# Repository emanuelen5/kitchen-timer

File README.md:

# Kitchen timer

We're building a Kitchen timer!
The project is heavily inspired by [REST: Kitchen timer by mkdxdx [Hackaday.io]](https://hackaday.io/project/194386-rest-kitchen-timer).

## Features

* ⏱️ Allows several timers to run in parallel
* ⚡ Is battery powered and power efficient
* 🔌 Charged by USB-C
* 💻 Programmable through the same USB port
* 🐍 Easter eggs

## Hardware

* Atmega328P as microcontroller
* Rotary encoder for setting the time
* 16x16 LED matrix as display
* 32 kHz crystal for accurate timekeeping
* Passive buzzer for beeping

See the bill of material in the KiCAD project for the full details.

### Mechanical components

Additionally, you will need the following mechanical components for the assembly:

Description                                               | Qty
--------------------------------------------------------- |-----
Hexagon Socket Button Head Screw ISO 7380-1 - M3 x 16     | 4
Hexagon Socket Button Head Screw ISO 7380-1 - M2 x        | 3
Brass Threaded Insert M3                                  | 4
Brass Threaded Insert M2                                  | 3
Hexagon Socket Button Head Screw ISO 7380-1 - M2 x        | 3
3.7V Lipo battery 1000mAh, 10x20x50mm, JST XH2.54 2 pin   | 1

### Manufacturing / gerber files

If you want to build the PCB yourself, you can download the latest release of Gerber files from Github: <https://github.com/emanuelen5/kitchen-timer/releases/latest>

### Enclosure

The .stl files are available in [./enclosure](./enclosure/) so you can 3D-print the enclosure yourself.

## Software

You can flash the program directly using the ISP header on the board if you want (the same procedure as flashing the bootloader, below). But it's more convenient to add the bootloader so you don't have to open up the enclosure for each software update. Then you can instead program it over the USB-C connector.

For that, you need the bootloader firmware and programmer software which you can download from <https://github.com/emanuelen5/kitchen-timer/releases/tag/bootloader-v1.2.0>.

### Bootloader

To flash the microcontroller with the bootloader, you need `avrdude`.
Avrdude 7.3 can be downloaded from <https://github.com/avrdudes/avrdude/releases/tag/v7.3>. Make sure to add it to your `PATH`.

Connect your programmer of choice to the 6-pin in-system programmer (ISP) connector: \

<!--
Attribution:
["6- and 10-pin AVR ISP headers"](https://en.wikipedia.org/wiki/In-system_programming#/media/File:Isp_headers.svg)
by osiixy (2013-01-05), used under [CC BY 3.0](https://creativecommons.org/licenses/by/3.0/).
Adaptations: removed 10-pin header and some text; improved the contrast for dark
             mode.
-->

Then run the following command (replace `<programmer>` with your programmer of choice, like `usbtiny`):

```bash
# the bootloader.hex file needs to be in the current directory
avrdude -p atmega328p -c <programmer> -U flash:w:bootloader.hex:i \
  -U lfuse:w:0x62:m -U hfuse:w:0xD0:m -U efuse:w:0xFF:m
```

> [!TIP]
> Use `avrdude -c ?` to see which programmers are available

This flashes the bootloader and sets the required fuses for the bootloader.

After that you can disconnect the programmer and assemble the device.

### Programmer

Now that you have the bootloader on the device, you can use the USB-C cable for programming it by using the programmer application.

#### Dependencies

First you will need to install some packages that the programmer needs (files from <https://github.com/emanuelen5/kitchen-timer/releases/tag/bootloader-v1.2.0>).

```bash
pip install -r ./programmer/requirements.txt
```

You can now program the application onto the device through the bootloader!

### Upload firmware

Download the latest revision of the firmware (if you want to build it yourself, see [#Development](#development) below) from the releases <https://github.com/emanuelen5/kitchen-timer/releases>.

Connect the USB cable to the device, and then run

```bash
python3 ./programmer/programmer.py --hexfile firmware.hex
```

## Development

### Firmware

To build the firmware, you need `pio` which can be downloaded from <https://pypi.org/project/platformio/> or installed using `pip` (the official Package Installer for Python)

To build any of the environments, use the `pio` command, like

```bash
# builds the main application and puts it in .pio/builds/application/firmware.hex
pio run -e application
```

Then use the programmer to upload the firmware to the device.

## Background

Our kitchen timer is an iteration of [mkdxdx](https://hackaday.io/mkdxdx) project "REST: Kitchen timerREST: Kitchen timer". We wanted to keep the "dial" (rotate-to-set) concept and the 16x16 led matrix but do it with an ATmega328p and a custom PCB.
In the end we scrapped the dial since the design became too complicated, and settled on a simpler design.

### Motivation

Both [Erasmus Cedernaes](https://github.com/emanuelen5) and [Nicolas Perozzi](https://github.com/nperozzi) belong to [Stockholm Makerspace](https://www.makerspace.se/). On the same day, we messaged each other a link to mkdxdx​ project. We were very excited about building something that would be "practical" so we decided to team up and work on this together. Additionally, we share an interest in working with the AVR MCUs. This project is a nice blend of programming, electrical, mechanical, 3d printing, and design but, without feeling overwhelming.

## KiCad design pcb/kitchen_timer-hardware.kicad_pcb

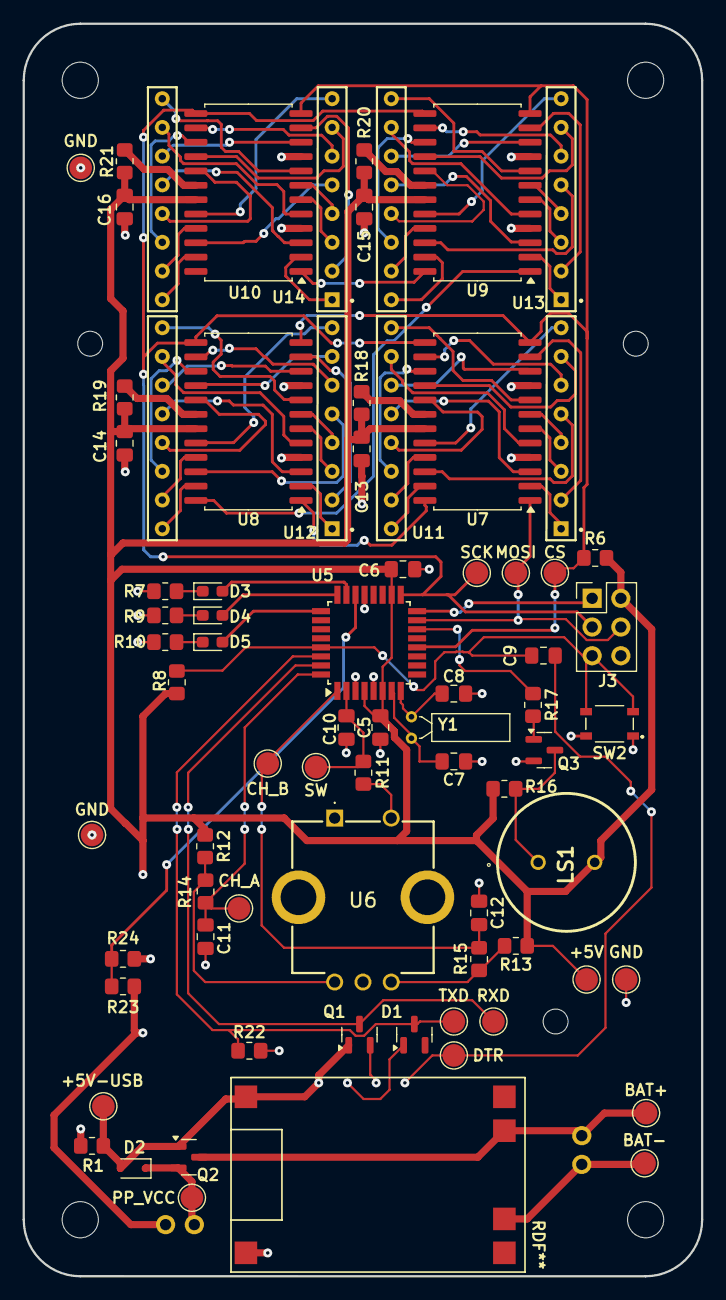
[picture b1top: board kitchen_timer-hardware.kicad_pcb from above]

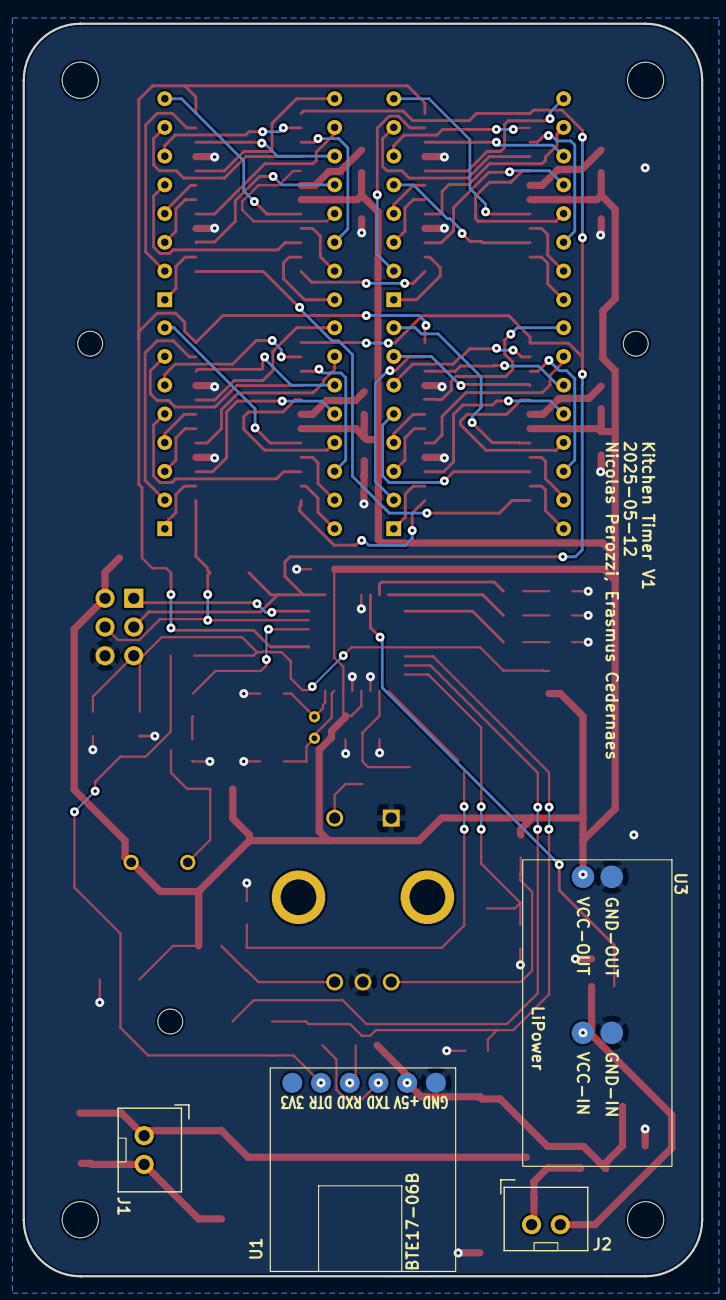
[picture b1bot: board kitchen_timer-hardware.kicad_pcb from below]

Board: 2 copper layers, 60.0 x 110.8 mm, 83 parts (4 on the bottom side), 106 nets.

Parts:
C5, C6, C9, C13, C14, C15, C16: 100nF; C_0805_2012Metric_Pad1.18x1.45mm_HandSolder
C7, C8: 22pF; C_0805_2012Metric_Pad1.18x1.45mm_HandSolder
C10, C11, C12: 10nF; C_0805_2012Metric_Pad1.18x1.45mm_HandSolder
D1: BAS40; SOT-23
D2: PMEG4010CEJ; D_SOD-323F
D3, D4, D5: Red test LED; LED_0603_1608Metric_Pad1.05x0.95mm_HandSolder
H1, H2, H7: MountingHole; MountingHole_2.2mm_M2
H3, H4, H5, H6: MountingHole; MountingHole_3.2mm_M3
J1: Conn_01x02; JST_XH_1x02_P2.54mm_Vertical
J2: Conn_01x02_Pin; JST_XH_1x02_P2.54mm_Vertical
J3: AVR-ISP-6; PinHeader_2x03_P2.54mm_Vertical
LS1: PS1240P02CT3; PS1240P02BT
Q1: JSM2302; SOT-23
Q2: IRLML6402; SOT-23
Q3: MMBT3904; MMBT3904 (SOT-23)
R1, R6, R8, R11, R12, R13, R14, R15, R22: 10k; R_0805_2012Metric_Pad1.20x1.40mm_HandSolder
R7, R9, R10, R16, R17: 1k; R_0805_2012Metric_Pad1.20x1.40mm_HandSolder
R18, R19, R20, R21: 62K; R_0805_2012Metric_Pad1.20x1.40mm_HandSolder
R23: 3.3M; R_0805_2012Metric_Pad1.20x1.40mm_HandSolder
R24: 1M; R_0805_2012Metric_Pad1.20x1.40mm_HandSolder
SW2: SKRPACE010; SW_SKRPACE010
TP1: MOSI; TestPoint_Pad_D2.0mm
TP2: TXD; TestPoint_Pad_D2.0mm
TP3: SCK; TestPoint_Pad_D2.0mm
TP4: RXD; TestPoint_Pad_D2.0mm
TP5: CS; TestPoint_Pad_D2.0mm
TP6: DTR; TestPoint_Pad_D2.0mm
TP7: +5V-USB; TestPoint_Pad_D2.0mm
TP8, TP14, TP15: GND; TestPoint_Pad_D2.0mm
TP9: CH_A; TestPoint_Pad_D2.0mm
TP10: CH_B; TestPoint_Pad_D2.0mm
TP11: SW; TestPoint_Pad_D2.0mm
TP12: +5V; TestPoint_Pad_D2.0mm
TP13: PP_VCC; TestPoint_Pad_D2.0mm
TP16: BAT+; TestPoint_Pad_D2.0mm
TP17: BAT-; TestPoint_Pad_D2.0mm
U1: CH340E UART Module; CH340E_UART_BREAKOUT
U2: TP4056 breakout; TP4056_BREAKOUT
U3: SparkFun_LiPower
U5: ATMEGA328P-AU; TQFP-32_7x7mm_P0.8mm
U6: PEC11R-4215F-S0024; PEC11R4215FS0024
U7, U8, U9, U10: MAX7219; SOIC-24W_7.5x15.4mm_P1.27mm
U11, U12, U13, U14: KWM-20882CUYB
Y1: Crystal-32kHz; Crystal_C26-LF_D2.1mm_L6.5mm_Horizontal

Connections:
+5V: C5.1, C6.1, C13.1, C14.1, C15.1, C16.1, J3.2 (VCC), LS1.2, R6.1, R8.1, R12.1, R13.1, R16.2, R18.1, R19.1, R20.1, R21.1, TP12.1, U3.3 (VCC_OUT), U5.4 (VCC), U5.6 (VCC), U5.18 (AVCC), U7.19 (V+), U8.19 (V+), U9.19 (V+), U10.19 (V+)
/+5V Boost Converter/BAT_VOLT: R23.2, R24.1, U5.22 (ADC7)
/+5V Boost Converter/PP_VCC: D2.1 (K), J2.1, Q2.2 (S), TP13.1
/BMS & Power Path/+5V-USB: D2.2 (A), Q1.1 (G), Q2.1 (G), R1.2, TP7.1, U1.5 (+5V), U2.1 (IN+)
/BMS & Power Path/BAT+: J1.1, Q2.3 (D), TP16.1, U2.4 (B+)
/BMS & Power Path/BAT-: J1.2, TP17.1, U2.5 (B-)
/LED Matrices Drivers/CS: R6.2, TP5.1, U5.12 (PB0), U7.12 (LOAD), U8.12 (LOAD), U9.12 (LOAD), U10.12 (LOAD)
/LED Matrices Drivers/MOSI: J3.4 (MOSI), TP1.1, U5.15 (PB3), U7.1 (DIN)
/LED Matrices Drivers/Mat1A.DIG_0: U7.2 (DIG_0), U11.01 (R1)
/LED Matrices Drivers/Mat1A.DIG_1: U7.11 (DIG_1), U11.02 (R2)
/LED Matrices Drivers/Mat1A.DIG_2: U7.6 (DIG_2), U11.03 (R3)
/LED Matrices Drivers/Mat1A.DIG_3: U7.7 (DIG_3), U11.04 (R4)
/LED Matrices Drivers/Mat1A.DIG_4: U7.3 (DIG_4), U11.12 (R5)
/LED Matrices Drivers/Mat1A.DIG_5: U7.10 (DIG_5), U11.11 (R6)
/LED Matrices Drivers/Mat1A.DIG_6: U7.5 (DIG_6), U11.10 (R7)
/LED Matrices Drivers/Mat1A.DIG_7: U7.8 (DIG_7), U11.09 (R8)
/LED Matrices Drivers/Mat1A.SEG_A: U7.14 (SEG_A), U11.06 (C2)
/LED Matrices Drivers/Mat1A.SEG_B: U7.16 (SEG_B), U11.07 (C3)
/LED Matrices Drivers/Mat1A.SEG_C: U7.20 (SEG_C), U11.08 (C4)
/LED Matrices Drivers/Mat1A.SEG_D: U7.23 (SEG_D), U11.16 (C5)
/LED Matrices Drivers/Mat1A.SEG_DP: U7.22 (SEG_DP), U11.05 (C1)
/LED Matrices Drivers/Mat1A.SEG_E: U7.21 (SEG_E), U11.15 (C6)
/LED Matrices Drivers/Mat1A.SEG_F: U7.15 (SEG_F), U11.14 (C7)
/LED Matrices Drivers/Mat1A.SEG_G: U7.17 (SEG_G), U11.13 (C8)
/LED Matrices Drivers/Mat1B.DIG_0: U8.2 (DIG_0), U12.01 (R1)
/LED Matrices Drivers/Mat1B.DIG_1: U8.11 (DIG_1), U12.02 (R2)
/LED Matrices Drivers/Mat1B.DIG_2: U8.6 (DIG_2), U12.03 (R3)
/LED Matrices Drivers/Mat1B.DIG_3: U8.7 (DIG_3), U12.04 (R4)
/LED Matrices Drivers/Mat1B.DIG_4: U8.3 (DIG_4), U12.12 (R5)
/LED Matrices Drivers/Mat1B.DIG_5: U8.10 (DIG_5), U12.11 (R6)
/LED Matrices Drivers/Mat1B.DIG_6: U8.5 (DIG_6), U12.10 (R7)
/LED Matrices Drivers/Mat1B.DIG_7: U8.8 (DIG_7), U12.09 (R8)
/LED Matrices Drivers/Mat1B.SEG_A: U8.14 (SEG_A), U12.06 (C2)
/LED Matrices Drivers/Mat1B.SEG_B: U8.16 (SEG_B), U12.07 (C3)
/LED Matrices Drivers/Mat1B.SEG_C: U8.20 (SEG_C), U12.08 (C4)
/LED Matrices Drivers/Mat1B.SEG_D: U8.23 (SEG_D), U12.16 (C5)
/LED Matrices Drivers/Mat1B.SEG_DP: U8.22 (SEG_DP), U12.05 (C1)
/LED Matrices Drivers/Mat1B.SEG_E: U8.21 (SEG_E), U12.15 (C6)
/LED Matrices Drivers/Mat1B.SEG_F: U8.15 (SEG_F), U12.14 (C7)
/LED Matrices Drivers/Mat1B.SEG_G: U8.17 (SEG_G), U12.13 (C8)
/LED Matrices Drivers/Mat2A.DIG_0: U9.2 (DIG_0), U13.01 (R1)
/LED Matrices Drivers/Mat2A.DIG_1: U9.11 (DIG_1), U13.02 (R2)
/LED Matrices Drivers/Mat2A.DIG_2: U9.6 (DIG_2), U13.03 (R3)
/LED Matrices Drivers/Mat2A.DIG_3: U9.7 (DIG_3), U13.04 (R4)
/LED Matrices Drivers/Mat2A.DIG_4: U9.3 (DIG_4), U13.12 (R5)
/LED Matrices Drivers/Mat2A.DIG_5: U9.10 (DIG_5), U13.11 (R6)
/LED Matrices Drivers/Mat2A.DIG_6: U9.5 (DIG_6), U13.10 (R7)
/LED Matrices Drivers/Mat2A.DIG_7: U9.8 (DIG_7), U13.09 (R8)
/LED Matrices Drivers/Mat2A.SEG_A: U9.14 (SEG_A), U13.06 (C2)
/LED Matrices Drivers/Mat2A.SEG_B: U9.16 (SEG_B), U13.07 (C3)
/LED Matrices Drivers/Mat2A.SEG_C: U9.20 (SEG_C), U13.08 (C4)
/LED Matrices Drivers/Mat2A.SEG_D: U9.23 (SEG_D), U13.16 (C5)
/LED Matrices Drivers/Mat2A.SEG_DP: U9.22 (SEG_DP), U13.05 (C1)
/LED Matrices Drivers/Mat2A.SEG_E: U9.21 (SEG_E), U13.15 (C6)
/LED Matrices Drivers/Mat2A.SEG_F: U9.15 (SEG_F), U13.14 (C7)
/LED Matrices Drivers/Mat2A.SEG_G: U9.17 (SEG_G), U13.13 (C8)
/LED Matrices Drivers/Mat2B.DIG_0: U10.2 (DIG_0), U14.01 (R1)
/LED Matrices Drivers/Mat2B.DIG_1: U10.11 (DIG_1), U14.02 (R2)
/LED Matrices Drivers/Mat2B.DIG_2: U10.6 (DIG_2), U14.03 (R3)
/LED Matrices Drivers/Mat2B.DIG_3: U10.7 (DIG_3), U14.04 (R4)
/LED Matrices Drivers/Mat2B.DIG_4: U10.3 (DIG_4), U14.12 (R5)
/LED Matrices Drivers/Mat2B.DIG_5: U10.10 (DIG_5), U14.11 (R6)
/LED Matrices Drivers/Mat2B.DIG_6: U10.5 (DIG_6), U14.10 (R7)
/LED Matrices Drivers/Mat2B.DIG_7: U10.8 (DIG_7), U14.09 (R8)
/LED Matrices Drivers/Mat2B.SEG_A: U10.14 (SEG_A), U14.06 (C2)
/LED Matrices Drivers/Mat2B.SEG_B: U10.16 (SEG_B), U14.07 (C3)
/LED Matrices Drivers/Mat2B.SEG_C: U10.20 (SEG_C), U14.08 (C4)
/LED Matrices Drivers/Mat2B.SEG_D: U10.23 (SEG_D), U14.16 (C5)
/LED Matrices Drivers/Mat2B.SEG_DP: U10.22 (SEG_DP), U14.05 (C1)
/LED Matrices Drivers/Mat2B.SEG_E: U10.21 (SEG_E), U14.15 (C6)
/LED Matrices Drivers/Mat2B.SEG_F: U10.15 (SEG_F), U14.14 (C7)
/LED Matrices Drivers/Mat2B.SEG_G: U10.17 (SEG_G), U14.13 (C8)
/LED Matrices Drivers/SCK: J3.3 (SCK), TP3.1, U5.17 (PB5), U7.13 (CLK), U8.13 (CLK), U9.13 (CLK), U10.13 (CLK)
/Microcontroller/DTR: C9.1, TP6.1, U1.2 (DTR)
/Microcontroller/ENCODER_CH_A: C11.1, R14.2, TP9.1, U5.32 (PD2)
/Microcontroller/ENCODER_CH_B: C12.1, R15.2, TP10.1, U5.1 (PD3)
/Microcontroller/MCU_RXD: D1.3 (K), R22.1, TP2.1, U5.30 (PD0)
/Microcontroller/MCU_TXD: Q1.3 (D), TP4.1, U5.31 (PD1)
/Microcontroller/MISO: J3.1 (MISO), U5.16 (PB4)
/Microcontroller/RESET: C9.2, J3.5 (~RST), R8.2, SW2.3, SW2.4, U5.29 (~RESET/PC6)
/Microcontroller/SPEAKER: R17.1, U5.14 (PB2)
/Microcontroller/SW: C10.1, R11.2, TP11.1, U5.2 (PD4)
/Microcontroller/TEST_LED1: D3.2 (A), U5.23 (PC0)
/Microcontroller/TEST_LED2: D4.2 (A), U5.24 (PC1)
/Microcontroller/TEST_LED3: D5.2 (A), U5.25 (PC2)
/Microcontroller/XTAL1: C7.1, U5.7 (XTAL1/PB6), Y1.1
/Microcontroller/XTAL2: C8.1, U5.8 (XTAL2/PB7), Y1.2 (CRYSTAL_2)
GND: C5.2, C6.2, C7.2, C8.2, C10.2, C11.2, C12.2, C13.2, C14.2, C15.2, C16.2, J3.6 (GND), Q3.2 (E), R1.1, R7.2, R9.2, R10.2, R22.2, R24.2, SW2.1, SW2.2, TP8.1, TP14.1, TP15.1, U1.6 (GND), U2.2 (IN-), U3.2 (GND-IN), U3.4 (GND_OUT), U5.3 (GND), U5.5 (GND), U5.21 (GND), U6.1 (COM), U6.C1 (COMMON), U7.4 (GND), U7.9 (GND), U8.4 (GND), U8.9 (GND), U9.4 (GND), U9.9 (GND), U10.4 (GND), U10.9 (GND)
unnamed: D1.1 (A), U1.4 (TXD)
unnamed: D3.1 (K), R7.1
unnamed: D4.1 (K), R9.1
unnamed: D5.1 (K), R10.1
unnamed: Q1.2 (S), U1.3 (RXD)
unnamed: Q3.1 (B), R17.2
unnamed: LS1.1, Q3.3 (C), R16.1
unnamed: R12.2, R14.1, U6.A1 (CHANNEL_A)
unnamed: R13.2, R15.1, U6.B1 (CHANNEL_B)
unnamed: R11.1, U6.2 (NO)
unnamed: U7.24 (DOUT), U8.1 (DIN)
unnamed: R18.2, U7.18 (ISET)
unnamed: U8.24 (DOUT), U9.1 (DIN)
unnamed: R19.2, U8.18 (ISET)
unnamed: R20.2, U9.18 (ISET)
unnamed: U9.24 (DOUT), U10.1 (DIN)
unnamed: R21.2, U10.18 (ISET)
PP_VCC_after_switch: J2.2, R23.1, U3.1 (VCC_IN)

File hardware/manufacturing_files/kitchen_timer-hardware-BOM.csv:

"Reference","Value","Footprint","Qty","Supplier Part #"
"C5,C6,C9,C13,C14,C15,C16","100nF","Capacitor_SMD:C_0805_2012Metric_Pad1.18x1.45mm_HandSolder","7","C77082"
"C7,C8","22pF","Capacitor_SMD:C_0805_2012Metric_Pad1.18x1.45mm_HandSolder","2","C1804"
"C10,C11,C12","10nF","Capacitor_SMD:C_0805_2012Metric_Pad1.18x1.45mm_HandSolder","3","C1710"
"D1","BAS40","Package_TO_SOT_SMD:SOT-23","1"," C77289"
"D2","PMEG4010CEJ","Diode_SMD:D_SOD-323F","1","C50704"
"D3,D4,D5","Red test LED","LED_SMD:LED_0603_1608Metric_Pad1.05x0.95mm_HandSolder","3","C965799"
"Q1","JSM2302","Package_TO_SOT_SMD:SOT-23","1"," C916403"
"Q2","IRLML6402","Package_TO_SOT_SMD:SOT-23","1","C2593"
"Q3","MMBT3904","kitchen_timer:MMBT3904 (SOT-23)","1"," C7420353"
"R1,R6,R8,R11,R12,R13,R14,R15","10k","Resistor_SMD:R_0805_2012Metric_Pad1.20x1.40mm_HandSolder","8","C17414"
"R7,R9,R10,R16,R17","1k","Resistor_SMD:R_0805_2012Metric_Pad1.20x1.40mm_HandSolder","5","C17513"
"R18,R19,R20,R21","62K","Resistor_SMD:R_0805_2012Metric_Pad1.20x1.40mm_HandSolder","4","C17783"
"SW2","SKRPACE010","kitchen_timer:SW_SKRPACE010","1","C139797"
"U5","ATMEGA328P-AU","Package_QFP:TQFP-32_7x7mm_P0.8mm","1","C14877"
"U7,U8,U9,U10","MAX7219","Package_SO:SOIC-24W_7.5x15.4mm_P1.27mm","4","C9964"
"LS1","PS1240P02CT3","kitchen_timer:PS1240P02BT","1"," C76873"
"U6","PEC11R-4215F-S0024","kitchen_timer:PEC11R4215FS0024","1","C143790"

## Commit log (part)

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2025-07-09 just added a TODO comment
2025-07-09 Made should_toggle... variables for clarity
2025-07-09 moved #include to the cpp file
2025-07-10 Completed the definition of the Hour Indicator
2025-07-10 changed the function name to draw_active_timer_indicator()
2025-07-10 added init_led_counter() to main
2025-07-15 added application_view enum and new variables into application_t
2025-07-16 Only call render once
2025-07-17 Created the fucntion change_view()
2025-07-17 Made const a couple of variables
2025-07-17 moved some #define to the confi.h file
2025-07-17 Create an Application Environment
2025-07-17 Added the open_new_timer()
2025-07-18 Simplified the render_active_timer_view() a little.
2025-07-20 Fixed a bug with allocating memory for the state machines
2025-07-20 changed the increment_current_time() for decrement_current_time
2025-07-21 I am getting rid of a redundant variable in the application_t struct
2025-07-23 Removed a variable that was not doing anything
2025-07-23 Made the press rotation skip timers that are in IDLE state.
2025-07-24 Modified service_application() so the active timer moves to the ringing timer.
2025-07-25 I made the RINGING state also blink the timer numbers also I restructured that blinking part of the code.
2025-07-25 bug: I added the set_state() function to pass from RINGING to IDLE
2025-07-25 I moved the digits offset one more column to the left to use the space better.
2025-07-26 Simplified the blinking of the Timer Indicator and Timer Digits by defining a struct for blink_state.
2025-07-26 Simplified a variable in draw_timers_indicator()
2025-07-27 Removed target_time from timer lib. It was unnecessary.
2025-07-27 Changes on the Unit test to include the SET_TIME state.
2025-07-27 changes to Unit test.
2025-07-27 Added sentinel value to application_view_t enum.
2025-07-27 Changed name of open_new_timer() to try_to_open_new_timer().
2025-07-27 Fixed a mistake in the name of try_to_open_new_timer() function
2025-07-28 Made the application_handle_event() into a set of special cases else, pass to the active state machine.
2025-07-28 created reset_state_machine()
2025-09-08 Added handle_encoder_rotation(), removed .pyc files and added that extension to .gitignore.
2025-09-08 changed from calculating interval to recording timestamps and bitshifting instead of division
2025-09-09 Created is_fast_step() in rotary-encoder.cpp
2025-09-09 Added the handling of the new events to the state machine
2025-09-10 Modified main.cpp in rotary-encoder environment
2025-09-10 Created the serial_commands library files
2025-09-10 Added str_equals() function in str-helper lib
2025-09-10 drafted the command_callbacks struct
2025-09-10 Added trim_string() to str-helper lib
2025-09-10 Break up into several functions
2025-09-10 Create type for speed of rotation
2025-09-10 Remove dead code
2025-09-10 Use event speed type
2025-09-10 Make fast rotations increment time faster than slow (#107)
    * Added handle_encoder_rotation(), removed .pyc files and added that
    extension to .gitignore.
    * Used a const instead of a preprocessor define
    * changed from calculating interval to recording timestamps and bitshifting instead of division
    * Added functionality: When it is over 1hr, the steps are 1min and if it is fast_steps, it is 5 mins steps
    * Created is_fast_step() in rotary-encoder.cpp
2025-09-12 Read pins earlier after interrupt
2025-09-12 Fix 'press, then rotate' bug
    When pressing and then rotating in short sequence, it would sometimes
    not register the first press, unless you waited for a long time between
    them.
    Fixes #96
2025-09-13 Shorten time before starting main application to ~0.6 secondds
2025-09-13 Make the timer beep when it finishes
2025-09-13 Fix linker issue for native tests
2025-09-14 Remove dead code in toneAC
    Fixes #97
2025-09-14 fixup! Repeat the beeps for an amount of times
2025-09-14 Fix: don't skip first note in melody
2025-09-14 fixup! Make the beat slightly shorter
2025-09-14 Clean up toneAC and make less generalized
    We have no use of those things, and they just take up storage space
    (plus an unused interrupt). It's more generalized than needed for our
    purpose.
    Fixes #97
2025-09-14 Rename functions
2025-09-14 Distinguish between time of hours and minutes
2025-09-20 Rename program->flash
2025-09-20 Remove TODOs
    It's better to track them as an issue. It only confuses the reader.
2025-09-20 Move files to Github
2025-09-23 Added the on_line_received() function (Dependency inversion) to separate UART logic form business logic.
2025-09-23 Added command + argument functionality
2025-09-24 In change_original_time() from timer lib, I changed the step argument from int16_t to int32_t to allow for a larger number of steps. This was needed for the parse_time_string(char* arg, uint32_t *ste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
2025-09-24 Added parse_time_string()
2025-09-24 Added commands for 'timer play', 'timer pause', 'timer reset'
2025-09-26 Modified UART_printf() to accept %d format with leading zeros
2025-09-30 Fixed a build problem on state_machine env.
2025-09-30 Created file for testing the serial_commands lib.
2025-10-01 Added setup brightness command
2025-10-01 Added setup volumne command.
2025-10-01 Fixed a bug in setup volume command.
2025-10-02 Added test buzzer command.
2025-10-03 moved led on/off into test commnad
2025-10-06 Use higher frequencies since the buzzer is tuned for 4kHz
2025-10-10 Make UART RX snappier
    Service the UART RX until it's empty.
2025-10-10 Remove unused declarations
2025-10-10 Autoformat files
2025-10-10 Remove redundant sketch
    The test cases already cover the counter, so the sketch itself doesn't
    serve a purpose anymore. There are several other sketches that offer
    similar and more complete examples.
2025-10-11 Implement simple power saving
    - Dim the display after 30 seconds of inactivity
    - Turn off the display after being dim for a minute without any timer
    running
    - Deep sleep not yet implemented
2025-10-11 Fixing a function that I deleted by mistake in during the merge
2025-10-14 added *.code-workspace to .gitignore
2025-10-15 Fix crash when interacting with rotary knob during power-on
    Interrupts got fired before all callbacks were initialized, leading to
    undefined behavior - and crashes.
    A crash could occur with the following conditions:
    1. Power on the device
    2. Rotate the knob (this would mark the INT1 interrupt as pending),
    before `init_hw_rotary_encoder()` is executed.
2025-10-17 Moved all remaining cbs and the command_callback_t struct definition.
2025-10-19 Break out function
2025-10-19 Remove unreachable statement
2025-10-24 Use compact conditional style
2025-10-24 Start writing tests for the main application
2025-10-29 Used bool in pad_zero variable
2025-10-29 Implemented unrecoginized_command() callback.
2025-10-31 Made pad_zero a bool
2025-10-31 Removed forgotten comments on wdt_bootloader_disable()
2025-10-31 Changed eeprom_write_byte() to eeprom_update_byte().
    The update function only writes if the new value is differen than the one stored. Better for saving writes in EEPROM.
2025-10-31 Changes the help_cmd cb to just help.
2025-10-31 Modified unrecoginized_command() to have a custom error message for brightness and volume setting.
2025-11-02 Fixed some problems with the merge.
2025-11-09 Go back to sleep if woken by an interrupt without user activity
    Turns out this is actually a completely valid case!
    The rotary encoder takes 4 substeps for each rotation, which thus makes
    up a very small angle of rotation. And that makes it likely to happen
    when just picking up the device, or shaking it lightly.
    If this happens, we'll quite quickly go to sleep again when the
    interrupts stop happening. That way we make sure to go down to low power
2025-11-09 Set int width to atmega328p size
    This way we can test natively using the same sized int.
2025-11-10 Changes to test_serial_commands unit test.
2025-11-12 Changes on the unit test
    Simplified the tests and put all the testing variables into a struct to make it easier to reset between tests.
2025-11-28 Changed activer_timer_view() in render module
2025-11-30 Added default state to render_active_timer_view()
2025-11-30 Added the change of target time during RUNNING and PAUSE mode.
2025-11-30 Created settings_menu module files
2025-11-30 Moved event_t to its own module.
2025-12-01 Started the settings_menu logic
2025-12-01 Added draw bitmap
2026-01-10 Reorganized the bytes in icon_brightness
2026-01-10 Removed a blank option after the back option
2026-01-10 Created the change_settings_views_callbacks_t struct to handle all settings_menu callbacks to change views.
2026-01-10 Added all settings views to application_view_t
2026-01-11 Removed an unnecessary function
2026-01-11 Changed change_to_a_setting_view_cb
2026-01-11 Created volume_setting_event_handling
2026-03-02 Make a separate function for getting icons
2026-03-04 Simplified current_menu_position and selected_setting for clarity
2026-03-04 Applied autoformat to render.cpp
2026-03-04 Fixed brightness over and underflow. Co-authored-by: Erasmus Cedernaes <github@emaus.dev>
2026-03-04 Moved down the icons
2026-03-04 Removed the MAX_BRIGHTNESS config
2026-03-04 We changed the test_buzzer melody on serial commands
2026-03-04 Fix mistake in 23736b24c2f617866299bd969b5b6892af003ecd
2026-03-06 Created the ten_beeps melody to avoid loading a repeated sequence at startup.
2026-03-06 Implemented the render function for the melody setting menu.
2026-03-06 Added comment to eeprom address enum
2026-03-06 Implemented the M1, M2,... render for melody settings
2026-03-11 Set CS to correct value before enabling its output
2026-03-11 Fixed saving volume
2026-03-11 Changed to reset_active_state_machine() when timer goes from RINGING to SET_TIME
2026-03-11 Fixed state machine test
2026-03-11 Break out function to describe intent and give single responsibility
2026-03-11 Go back to the settings from battery view
2026-03-14 Added Tx resistor, voltage devider for battery voltage mesurement.
2026-03-16 Cap the brightness if memory is uninitialized/corrupt
2026-03-22 Print debug UART output to the terminal
2026-03-22 Run interactive by default
2026-03-25 Created snake project.
2026-03-25 Removed food visibility flag not used
2026-04-01 Initialize battery measurement before starting it
    Fixes #165
2026-04-01 Remove unused field
2026-04-12 Check if next position is occupied by body _before_ moving the snake
    By rewriting it this way we always use the same argument to the function.
2026-04-12 Move calculation of the head
    It makes more sense to never set the head to an invalid position, but rather calculate its next position correctly from the start.
2026-04-12 Don't pass the next head as argument; rely on the compiler to deduplicate
2026-04-12 Reduce memory usage of snake by 446 B
    The memory is compressed by only storing the position of each body part relative
    to the previous one. That information can be stored in 2 bits per body part,
    instead of 2 byte per body part (16 bits) => roughly 1/8 the amount of memory is
    needed.
    - Before we used 16 * 16 * 2 B to store each body part's position = 512 B
    - Now we use 2 bits per body part + 2 B to store the head = 66 B
2026-04-14 Rename to warm_up_oscillator_circuit and call it inside init_hw_timer2_to_1s_interrupt
    Agent-Logs-Url: https://github.com/emanuelen5/kitchen-timer/sessions/97ecbdaf-337d-436e-b106-f3946e0ae6d6
2026-04-15 Scale the steps size more when going fast
2026-04-15 Make the menu indicator two pixels wide
2026-04-15 Start at the first menu option when opening menu
2026-04-15 Refactor state machine to use struct methods
2026-04-16 Fix fast-rotation snapping in RUNNING/PAUSED state
    Agent-Logs-Url: https://github.com/emanuelen5/kitchen-timer/sessions/0268891c-b359-484a-bbbd-76de6f052e8f
2026-04-18 Inline function
2026-04-18 React to presses faster
    This setting should perhaps be customizable. Different people might
    prefer different lengths. I prefer it snappy.
2026-04-18 Raise Für Elise two octaves
    The buzzer has slightly better frequency response in the higher region.
2026-04-22 Auto-format readme
2026-04-22 Move the background to the end
2026-04-22 Fill in details on how to program the device
2026-04-23 Add super-mario melody
2026-04-23 Add a script for previewing melodies
2026-04-23 Add a serial command for playing a melody
2026-04-23 Fix spelling mistake
2026-04-23 Play melody only once on test
